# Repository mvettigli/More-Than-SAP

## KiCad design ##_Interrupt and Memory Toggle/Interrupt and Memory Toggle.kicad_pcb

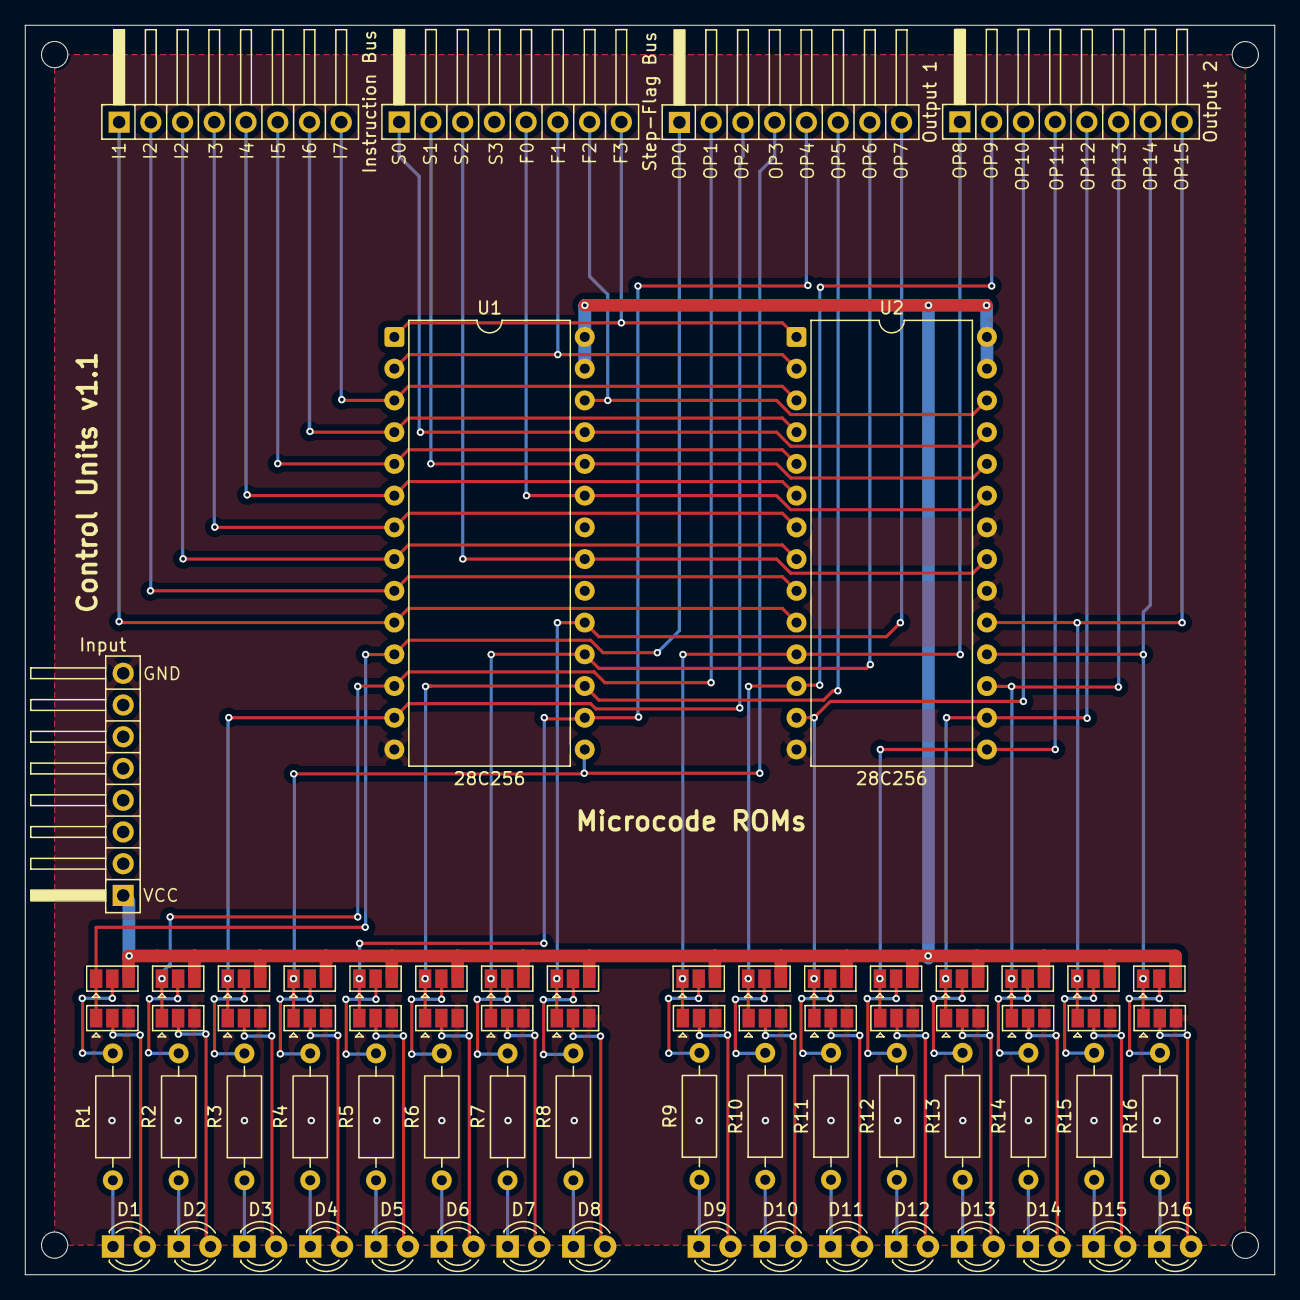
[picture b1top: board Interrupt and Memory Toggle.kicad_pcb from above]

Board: 2 copper layers, 100.0 x 100.0 mm, 71 parts (0 on the bottom side), 81 nets.

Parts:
D1, D2, D3, D4, D5, D6, D7, D8, D9, D10, D11, D12, D13, D14, D15, D16: YEL; LED_D3.0mm
J1: Input; PinHeader_1x08_P2.54mm_Horizontal
J2: Instruction Bus; PinHeader_1x08_P2.54mm_Horizontal
J3: Step-Flag Bus; PinHeader_1x08_P2.54mm_Horizontal
J4: Output 1; PinHeader_1x08_P2.54mm_Horizontal
J5: Output 2; PinHeader_1x08_P2.54mm_Horizontal
JP1, JP2, JP3, JP4, JP5, JP6, JP7, JP8, JP9, JP10, JP11, JP12, JP13, JP14, JP15, JP16, JP17, JP18, JP19, JP20, JP21, JP22, JP23, JP24, JP25, JP26, JP27, JP28, JP29, JP30, JP31, JP32: SolderJumper-3_P1.3mm_Open_Pad1.0x1.5mm
R1, R2, R3, R4, R5, R6, R7, R8, R9, R10, R11, R12, R13, R14, R15, R16: 220; R_Axial_DIN0207_L6.3mm_D2.5mm_P10.16mm_Horizontal
U1, U2: 28C256; DIP-28_W15.24mm

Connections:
/F0: J3.5, U1.23 (A11), U2.23 (A11)
/F1: J3.6, U1.2 (A12), U2.2 (A12)
/F2: J3.7, U1.26 (A13), U2.26 (A13)
/F3: J3.8, U1.1 (A14), U2.1 (A14)
/GND: J1.8, JP1.3 (B), JP3.3 (B), JP5.3 (B), JP7.3 (B), JP9.3 (B), JP11.3 (B), JP13.3 (B), JP15.3 (B), JP17.3 (B), JP19.3 (B), JP21.3 (B), JP23.3 (B), JP25.3 (B), JP27.3 (B), JP29.3 (B), JP31.3 (B), U1.14 (GND), U1.20 (~CS), U1.22 (~OE), U2.14 (GND), U2.20 (~CS), U2.22 (~OE)
/I0: J2.1, U1.10 (A0), U2.10 (A0)
/I1: J2.2, U1.9 (A1), U2.9 (A1)
/I2: J2.3, U1.8 (A2), U2.8 (A2)
/I3: J2.4, U1.7 (A3), U2.7 (A3)
/I4: J2.5, U1.6 (A4), U2.6 (A4)
/I5: J2.6, U1.5 (A5), U2.5 (A5)
/I6: J2.7, U1.4 (A6), U2.4 (A6)
/I7: J2.8, U1.3 (A7), U2.3 (A7)
/OP0: J4.1, JP1.1 (A), JP2.1 (A), U1.11 (D0)
/OP1: J4.2, JP3.1 (A), JP4.1 (A), U1.12 (D1)
/OP2: J4.3, JP5.1 (A), JP6.1 (A), U1.13 (D2)
/OP3: J4.4, JP7.1 (A), JP8.1 (A), U1.15 (D3)
/OP4: J4.5, JP9.1 (A), JP10.1 (A), U1.16 (D4)
/OP5: J4.6, JP11.1 (A), JP12.1 (A), U1.17 (D5)
/OP6: J4.7, JP13.1 (A), JP14.1 (A), U1.18 (D6)
/OP7: J4.8, JP15.1 (A), JP16.1 (A), U1.19 (D7)
/OP8: J5.1, JP17.1 (A), JP18.1 (A), U2.11 (D0)
/OP9: J5.2, JP19.1 (A), JP20.1 (A), U2.12 (D1)
/OP10: J5.3, JP21.1 (A), JP22.1 (A), U2.13 (D2)
/OP11: J5.4, JP23.1 (A), JP24.1 (A), U2.15 (D3)
/OP12: J5.5, JP25.1 (A), JP26.1 (A), U2.16 (D4)
/OP13: J5.6, JP27.1 (A), JP28.1 (A), U2.17 (D5)
/OP14: J5.7, JP31.1 (A), JP32.1 (A), U2.18 (D6)
/OP15: J5.8, JP29.1 (A), JP30.1 (A), U2.19 (D7)
/S0: J3.1, U1.25 (A8), U2.25 (A8)
/S1: J3.2, U1.24 (A9), U2.24 (A9)
/S2: J3.3, U1.21 (A10), U2.21 (A10)
/VCC: J1.1, JP2.3 (B), JP4.3 (B), JP6.3 (B), JP8.3 (B), JP10.3 (B), JP12.3 (B), JP14.3 (B), JP16.3 (B), JP18.3 (B), JP20.3 (B), JP22.3 (B), JP24.3 (B), JP26.3 (B), JP28.3 (B), JP30.3 (B), JP32.3 (B), U1.27 (~WE), U1.28 (VCC), U2.27 (~WE), U2.28 (VCC)
unnamed: D1.2 (A), JP1.2 (C)
unnamed: D1.1 (K), R1.1
unnamed: D2.2 (A), JP3.2 (C)
unnamed: D2.1 (K), R2.1
unnamed: D3.2 (A), JP5.2 (C)
unnamed: D3.1 (K), R3.1
unnamed: D4.2 (A), JP7.2 (C)
unnamed: D4.1 (K), R4.1
unnamed: D5.2 (A), JP9.2 (C)
unnamed: D5.1 (K), R5.1
unnamed: D6.2 (A), JP11.2 (C)
unnamed: D6.1 (K), R6.1
unnamed: D7.2 (A), JP13.2 (C)
unnamed: D7.1 (K), R7.1
unnamed: D8.2 (A), JP15.2 (C)
unnamed: D8.1 (K), R8.1
unnamed: D9.2 (A), JP17.2 (C)
unnamed: D9.1 (K), R9.1
unnamed: D10.2 (A), JP19.2 (C)
unnamed: D10.1 (K), R10.1
unnamed: D11.2 (A), JP21.2 (C)
unnamed: D11.1 (K), R11.1
unnamed: D12.2 (A), JP23.2 (C)
unnamed: D12.1 (K), R12.1
unnamed: D13.2 (A), JP25.2 (C)
unnamed: D13.1 (K), R13.1
unnamed: D14.2 (A), JP27.2 (C)
unnamed: D14.1 (K), R14.1
unnamed: D15.2 (A), JP29.2 (C)
unnamed: D15.1 (K), R15.1
unnamed: D16.2 (A), JP31.2 (C)
unnamed: D16.1 (K), R16.1
unnamed: JP2.2 (C), R1.2
unnamed: JP4.2 (C), R2.2
unnamed: JP6.2 (C), R3.2
unnamed: JP8.2 (C), R4.2
unnamed: JP10.2 (C), R5.2
unnamed: JP12.2 (C), R6.2
unnamed: JP14.2 (C), R7.2
unnamed: JP16.2 (C), R8.2
unnamed: JP18.2 (C), R9.2
unnamed: JP20.2 (C), R10.2
unnamed: JP22.2 (C), R11.2
unnamed: JP24.2 (C), R12.2
unnamed: JP26.2 (C), R13.2
unnamed: JP28.2 (C), R14.2
unnamed: JP30.2 (C), R15.2
unnamed: JP32.2 (C), R16.2

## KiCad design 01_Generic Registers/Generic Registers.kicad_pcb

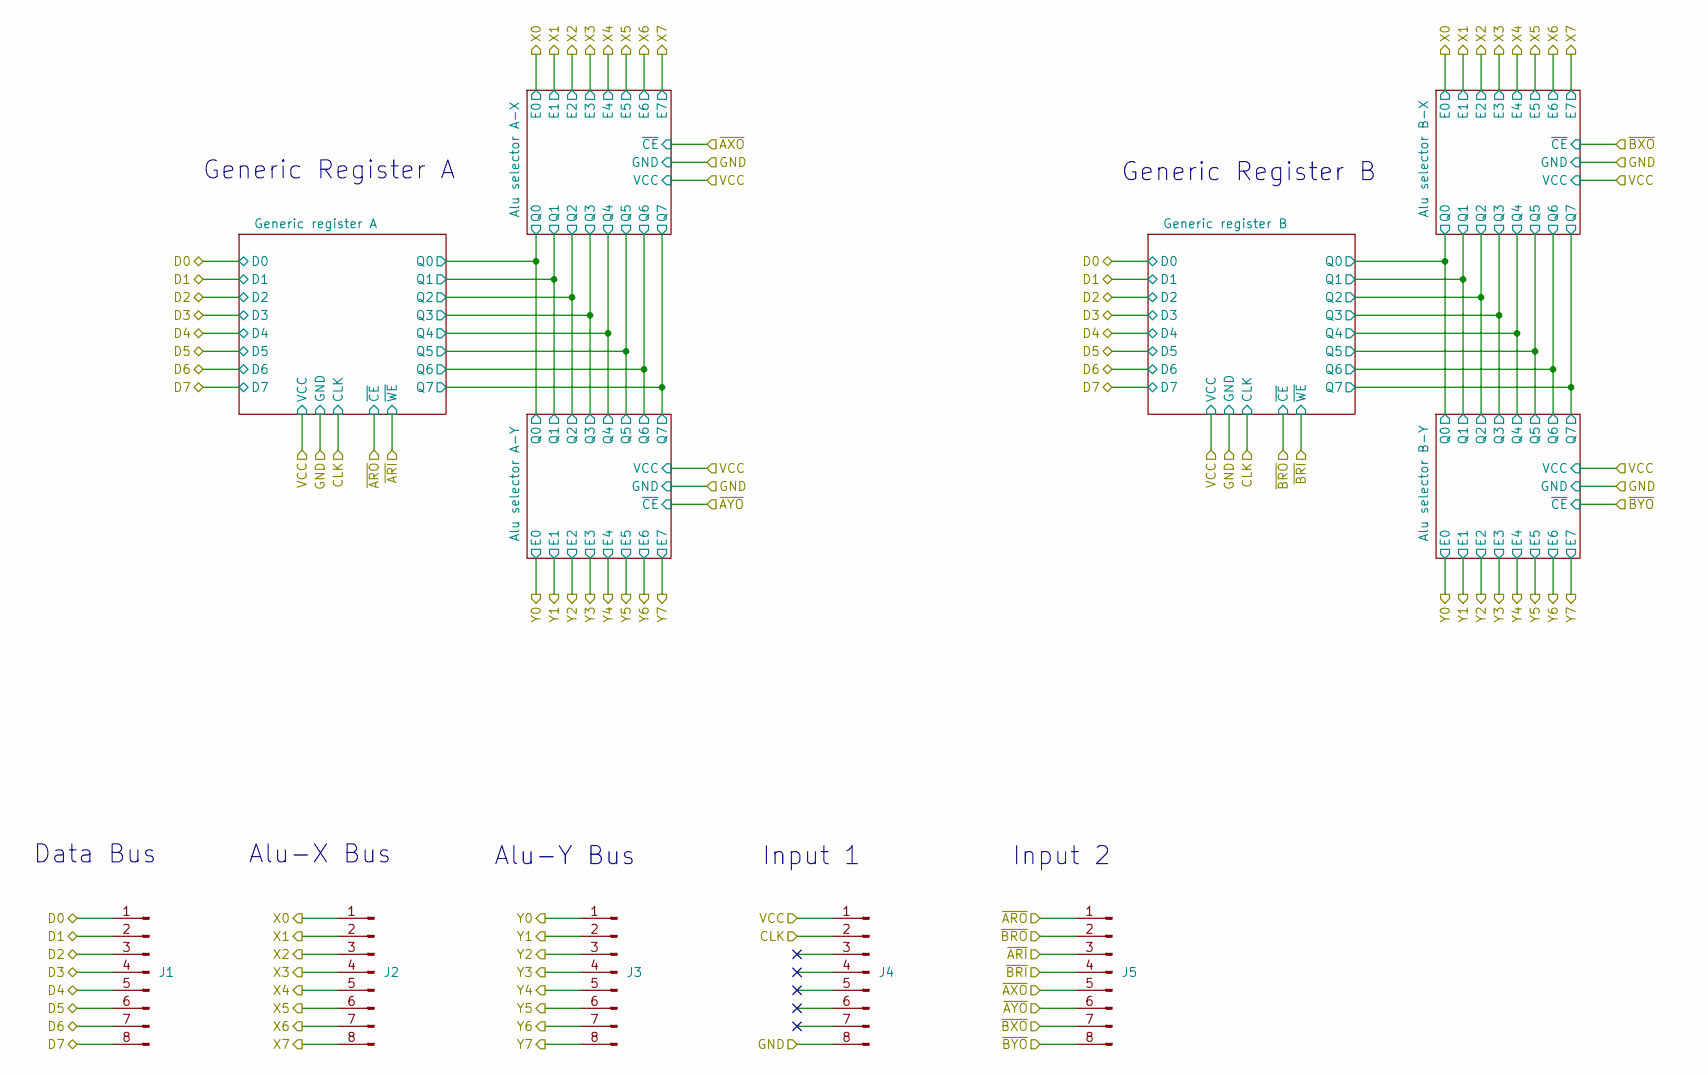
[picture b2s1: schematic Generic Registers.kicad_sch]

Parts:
J1: Data Bus; PinHeader_1x08_P2.54mm_Horizontal
J2: Alu-X Bus; PinHeader_1x08_P2.54mm_Horizontal
J3: Alu-Y Bus; PinHeader_1x08_P2.54mm_Horizontal
J4: Input 1; PinHeader_1x08_P2.54mm_Horizontal
J5: Input 2; PinHeader_1x08_P2.54mm_Horizontal

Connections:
/CLK: J4.2; also elsewhere on the board
/D0: J1.1; also elsewhere on the board
/D1: J1.2; also elsewhere on the board
/D2: J1.3; also elsewhere on the board
/D3: J1.4; also elsewhere on the board
/D4: J1.5; also elsewhere on the board
/D5: J1.6; also elsewhere on the board
/D6: J1.7; also elsewhere on the board
/D7: J1.8; also elsewhere on the board
/GND: J4.8; also elsewhere on the board
/VCC: J4.1; also elsewhere on the board
/X0: J2.1; also elsewhere on the board
/X1: J2.2; also elsewhere on the board
/X2: J2.3; also elsewhere on the board
/X3: J2.4; also elsewhere on the board
/X4: J2.5; also elsewhere on the board
/X5: J2.6; also elsewhere on the board
/X6: J2.7; also elsewhere on the board
/X7: J2.8; also elsewhere on the board
/Y0: J3.1; also elsewhere on the board
/Y1: J3.2; also elsewhere on the board
/Y2: J3.3; also elsewhere on the board
/Y3: J3.4; also elsewhere on the board
/Y4: J3.5; also elsewhere on the board
/Y5: J3.6; also elsewhere on the board
/Y6: J3.7; also elsewhere on the board
/Y7: J3.8; also elsewhere on the board
/~ARI: J5.3; also elsewhere on the board
/~ARO: J5.1; also elsewhere on the board
/~AXO: J5.5; also elsewhere on the board
/~AYO: J5.6; also elsewhere on the board
/~BRI: J5.4; also elsewhere on the board
/~BRO: J5.2; also elsewhere on the board
/~BXO: J5.7; also elsewhere on the board
/~BYO: J5.8; also elsewhere on the board

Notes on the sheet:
Generic Register A
Input 2
Alu-X Bus
Alu-Y Bus
Input 1
Data Bus
Generic Register B

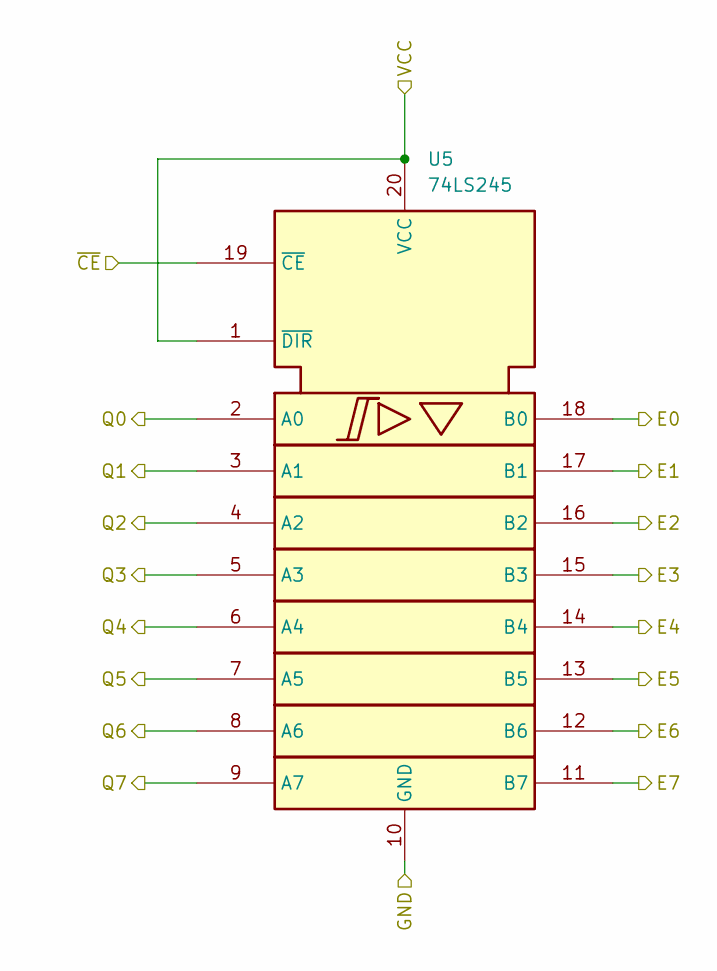
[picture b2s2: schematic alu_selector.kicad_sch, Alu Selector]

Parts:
U5: 74LS245; DIP-20_W7.62mm

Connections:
/Alu selector A-X/Q0: U5.2 (A0); also elsewhere on the board
/Alu selector A-X/Q1: U5.3 (A1); also elsewhere on the board
/Alu selector A-X/Q2: U5.4 (A2); also elsewhere on the board
/Alu selector A-X/Q3: U5.5 (A3); also elsewhere on the board
/Alu selector A-X/Q4: U5.6 (A4); also elsewhere on the board
/Alu selector A-X/Q5: U5.7 (A5); also elsewhere on the board
/Alu selector A-X/Q6: U5.8 (A6); also elsewhere on the board
/Alu selector A-X/Q7: U5.9 (A7); also elsewhere on the board
/GND: U5.10 (GND); also elsewhere on the board
/VCC: U5.1 (~DIR), U5.20 (VCC); also elsewhere on the board
/X0: U5.18 (B0); also elsewhere on the board
/X1: U5.17 (B1); also elsewhere on the board
/X2: U5.16 (B2); also elsewhere on the board
/X3: U5.15 (B3); also elsewhere on the board
/X4: U5.14 (B4); also elsewhere on the board
/X5: U5.13 (B5); also elsewhere on the board
/X6: U5.12 (B6); also elsewhere on the board
/X7: U5.11 (B7); also elsewhere on the board
/~AXO: U5.19 (~CE); also elsewhere on the board

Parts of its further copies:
U6, U7, U8: 74LS245; DIP-20_W7.62mm

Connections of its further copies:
/Alu selector A-X/Q0: U6.2 (A0); also elsewhere on the board
/Alu selector A-X/Q1: U6.3 (A1); also elsewhere on the board
/Alu selector A-X/Q2: U6.4 (A2); also elsewhere on the board
/Alu selector A-X/Q3: U6.5 (A3); also elsewhere on the board
/Alu selector A-X/Q4: U6.6 (A4); also elsewhere on the board
/Alu selector A-X/Q5: U6.7 (A5); also elsewhere on the board
/Alu selector A-X/Q6: U6.8 (A6); also elsewhere on the board
/Alu selector A-X/Q7: U6.9 (A7); also elsewhere on the board
/Alu selector B-X/Q0: U7.2 (A0), U8.2 (A0); also elsewhere on the board
/Alu selector B-X/Q1: U7.3 (A1), U8.3 (A1); also elsewhere on the board
/Alu selector B-X/Q2: U7.4 (A2), U8.4 (A2); also elsewhere on the board
/Alu selector B-X/Q3: U7.5 (A3), U8.5 (A3); also elsewhere on the board
/Alu selector B-X/Q4: U7.6 (A4), U8.6 (A4); also elsewhere on the board
/Alu selector B-X/Q5: U7.7 (A5), U8.7 (A5); also elsewhere on the board
/Alu selector B-X/Q6: U7.8 (A6), U8.8 (A6); also elsewhere on the board
/Alu selector B-X/Q7: U7.9 (A7), U8.9 (A7); also elsewhere on the board
/GND: U6.10 (GND), U7.10 (GND), U8.10 (GND); also elsewhere on the board
/VCC: U6.1 (~DIR), U6.20 (VCC), U7.1 (~DIR), U7.20 (VCC), U8.1 (~DIR), U8.20 (VCC); also elsewhere on the board
/X0: U7.18 (B0); also elsewhere on the board
/X1: U7.17 (B1); also elsewhere on the board
/X2: U7.16 (B2); also elsewhere on the board
/X3: U7.15 (B3); also elsewhere on the board
/X4: U7.14 (B4); also elsewhere on the board
/X5: U7.13 (B5); also elsewhere on the board
/X6: U7.12 (B6); also elsewhere on the board
/X7: U7.11 (B7); also elsewhere on the board
/Y0: U6.18 (B0), U8.18 (B0); also elsewhere on the board
/Y1: U6.17 (B1), U8.17 (B1); also elsewhere on the board
/Y2: U6.16 (B2), U8.16 (B2); also elsewhere on the board
/Y3: U6.15 (B3), U8.15 (B3); also elsewhere on the board
/Y4: U6.14 (B4), U8.14 (B4); also elsewhere on the board
/Y5: U6.13 (B5), U8.13 (B5); also elsewhere on the board
/Y6: U6.12 (B6), U8.12 (B6); also elsewhere on the board
/Y7: U6.11 (B7), U8.11 (B7); also elsewhere on the board
/~AYO: U6.19 (~CE); also elsewhere on the board
/~BXO: U7.19 (~CE); also elsewhere on the board
/~BYO: U8.19 (~CE); also elsewhere on the board

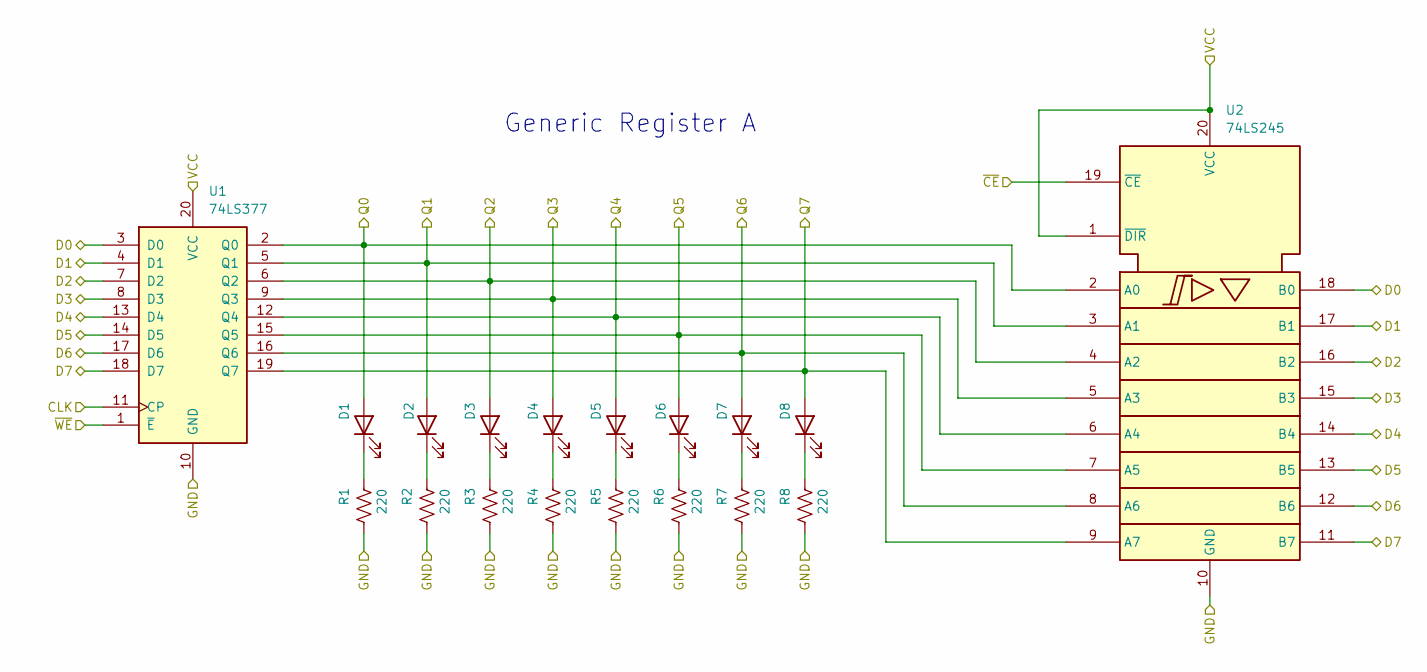
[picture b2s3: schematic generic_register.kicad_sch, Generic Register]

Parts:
D1, D2, D3, D4, D5, D6, D7, D8: RED; LED_D3.0mm
R1, R2, R3, R4, R5, R6, R7, R8: 220; R_Axial_DIN0207_L6.3mm_D2.5mm_P10.16mm_Horizontal
U1: 74LS377; DIP-20_W7.62mm
U2: 74LS245; DIP-20_W7.62mm

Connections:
/Alu selector A-X/Q0: D1.2 (A), U1.2 (Q0), U2.2 (A0); also elsewhere on the board
/Alu selector A-X/Q1: D2.2 (A), U1.5 (Q1), U2.3 (A1); also elsewhere on the board
/Alu selector A-X/Q2: D3.2 (A), U1.6 (Q2), U2.4 (A2); also elsewhere on the board
/Alu selector A-X/Q3: D4.2 (A), U1.9 (Q3), U2.5 (A3); also elsewhere on the board
/Alu selector A-X/Q4: D5.2 (A), U1.12 (Q4), U2.6 (A4); also elsewhere on the board
/Alu selector A-X/Q5: D6.2 (A), U1.15 (Q5), U2.7 (A5); also elsewhere on the board
/Alu selector A-X/Q6: D7.2 (A), U1.16 (Q6), U2.8 (A6); also elsewhere on the board
/Alu selector A-X/Q7: D8.2 (A), U1.19 (Q7), U2.9 (A7); also elsewhere on the board
/CLK: U1.11 (CP); also elsewhere on the board
/D0: U1.3 (D0), U2.18 (B0); also elsewhere on the board
/D1: U1.4 (D1), U2.17 (B1); also elsewhere on the board
/D2: U1.7 (D2), U2.16 (B2); also elsewhere on the board
/D3: U1.8 (D3), U2.15 (B3); also elsewhere on the board
/D4: U1.13 (D4), U2.14 (B4); also elsewhere on the board
/D5: U1.14 (D5), U2.13 (B5); also elsewhere on the board
/D6: U1.17 (D6), U2.12 (B6); also elsewhere on the board
/D7: U1.18 (D7), U2.11 (B7); also elsewhere on the board
/GND: R1.2, R2.2, R3.2, R4.2, R5.2, R6.2, R7.2, R8.2, U1.10 (GND), U2.10 (GND); also elsewhere on the board
/VCC: U1.20 (VCC), U2.1 (~DIR), U2.20 (VCC); also elsewhere on the board
/~ARI: U1.1 (~E); also elsewhere on the board
/~ARO: U2.19 (~CE); also elsewhere on the board
unnamed: D1.1 (K), R1.1
unnamed: D2.1 (K), R2.1
unnamed: D3.1 (K), R3.1
unnamed: D4.1 (K), R4.1
unnamed: D5.1 (K), R5.1
unnamed: D6.1 (K), R6.1
unnamed: D7.1 (K), R7.1
unnamed: D8.1 (K), R8.1

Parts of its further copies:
D9, D10, D11, D12, D13, D14, D15, D16: RED; LED_D3.0mm
R9, R10, R11, R12, R13, R14, R15, R16: 220; R_Axial_DIN0207_L6.3mm_D2.5mm_P10.16mm_Horizontal
U3: 74LS377; DIP-20_W7.62mm
U4: 74LS245; DIP-20_W7.62mm

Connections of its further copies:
/Alu selector B-X/Q0: D9.2 (A), U3.2 (Q0), U4.2 (A0); also elsewhere on the board
/Alu selector B-X/Q1: D10.2 (A), U3.5 (Q1), U4.3 (A1); also elsewhere on the board
/Alu selector B-X/Q2: D11.2 (A), U3.6 (Q2), U4.4 (A2); also elsewhere on the board
/Alu selector B-X/Q3: D12.2 (A), U3.9 (Q3), U4.5 (A3); also elsewhere on the board
/Alu selector B-X/Q4: D13.2 (A), U3.12 (Q4), U4.6 (A4); also elsewhere on the board
/Alu selector B-X/Q5: D14.2 (A), U3.15 (Q5), U4.7 (A5); also elsewhere on the board
/Alu selector B-X/Q6: D15.2 (A), U3.16 (Q6), U4.8 (A6); also elsewhere on the board
/Alu selector B-X/Q7: D16.2 (A), U3.19 (Q7), U4.9 (A7); also elsewhere on the board
/CLK: U3.11 (CP); also elsewhere on the board
/D0: U3.3 (D0), U4.18 (B0); also elsewhere on the board
/D1: U3.4 (D1), U4.17 (B1); also elsewhere on the board
/D2: U3.7 (D2), U4.16 (B2); also elsewhere on the board
/D3: U3.8 (D3), U4.15 (B3); also elsewhere on the board
/D4: U3.13 (D4), U4.14 (B4); also elsewhere on the board
/D5: U3.14 (D5), U4.13 (B5); also elsewhere on the board
/D6: U3.17 (D6), U4.12 (B6); also elsewhere on the board
/D7: U3.18 (D7), U4.11 (B7); also elsewhere on the board
/GND: R9.2, R10.2, R11.2, R12.2, R13.2, R14.2, R15.2, R16.2, U3.10 (GND), U4.10 (GND); also elsewhere on the board
/VCC: U3.20 (VCC), U4.1 (~DIR), U4.20 (VCC); also elsewhere on the board
/~BRI: U3.1 (~E); also elsewhere on the board
/~BRO: U4.19 (~CE); also elsewhere on the board
unnamed: D9.1 (K), R9.1
unnamed: D10.1 (K), R10.1
unnamed: D11.1 (K), R11.1
unnamed: D12.1 (K), R12.1
unnamed: D13.1 (K), R13.1
unnamed: D14.1 (K), R14.1
unnamed: D15.1 (K), R15.1
unnamed: D16.1 (K), R16.1

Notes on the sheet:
Generic Register A

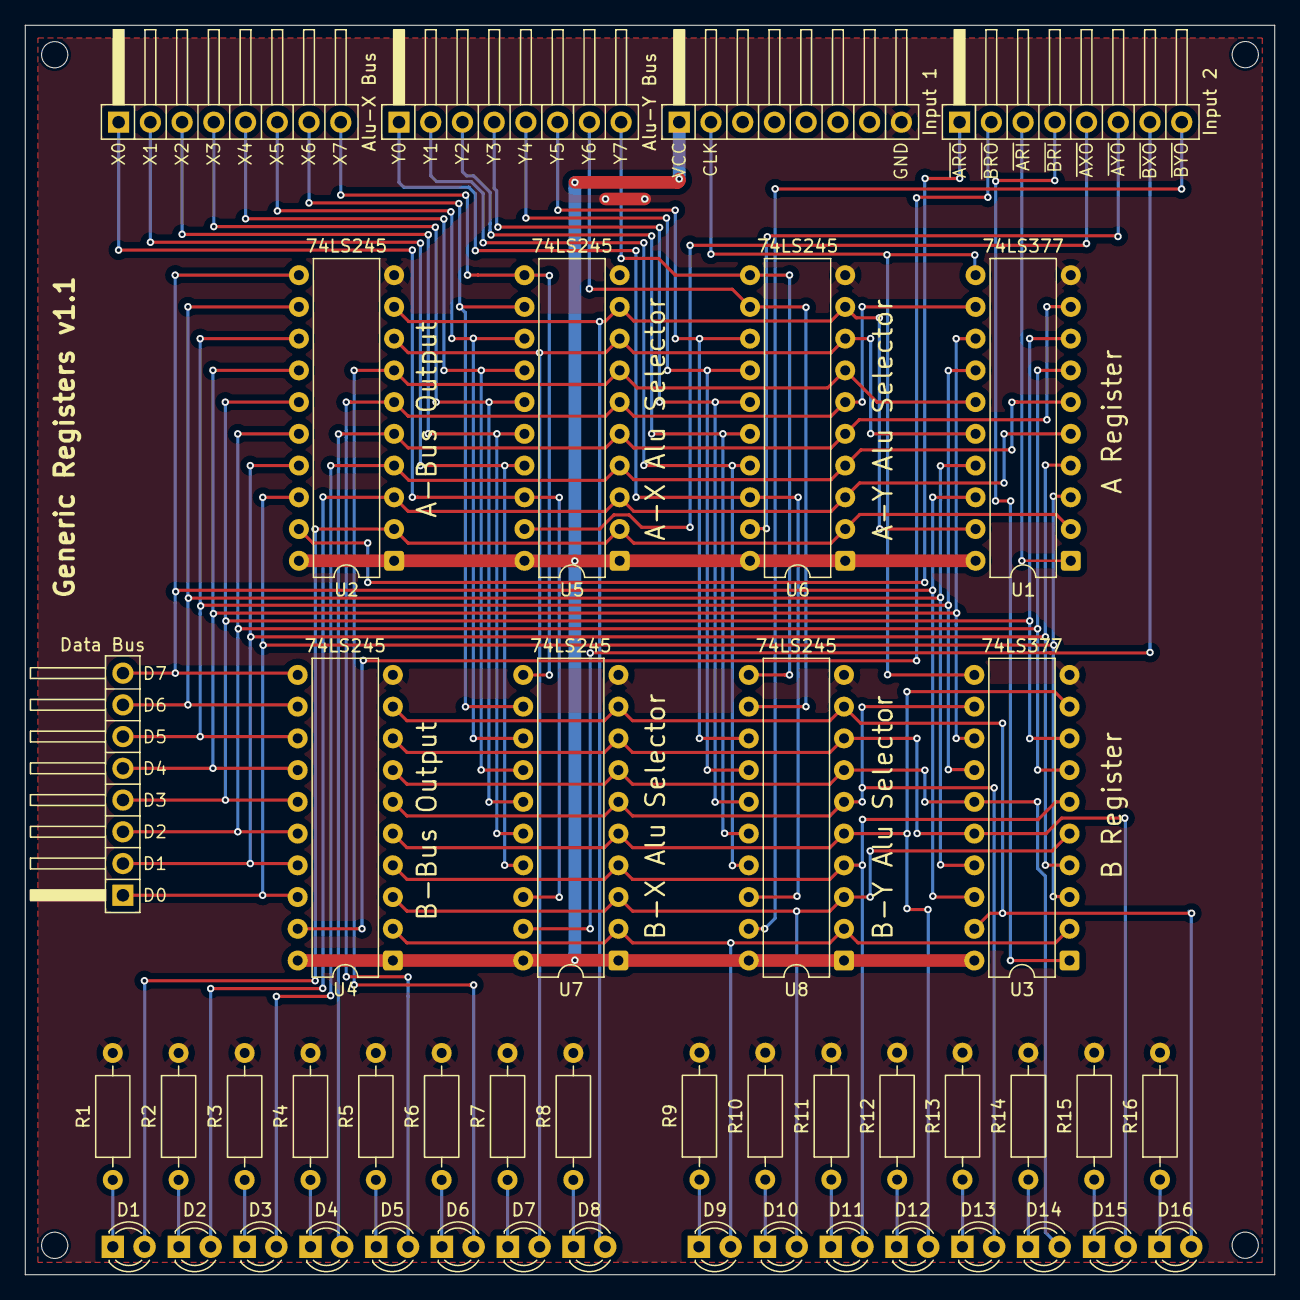
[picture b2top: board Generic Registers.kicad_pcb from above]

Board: 2 copper layers, 100.0 x 100.0 mm, 49 parts (0 on the bottom side), 67 nets.

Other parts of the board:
LU: MountingHole_2.1mm
LU#2, LU#3, LU#4: MountingHole_2.1mm

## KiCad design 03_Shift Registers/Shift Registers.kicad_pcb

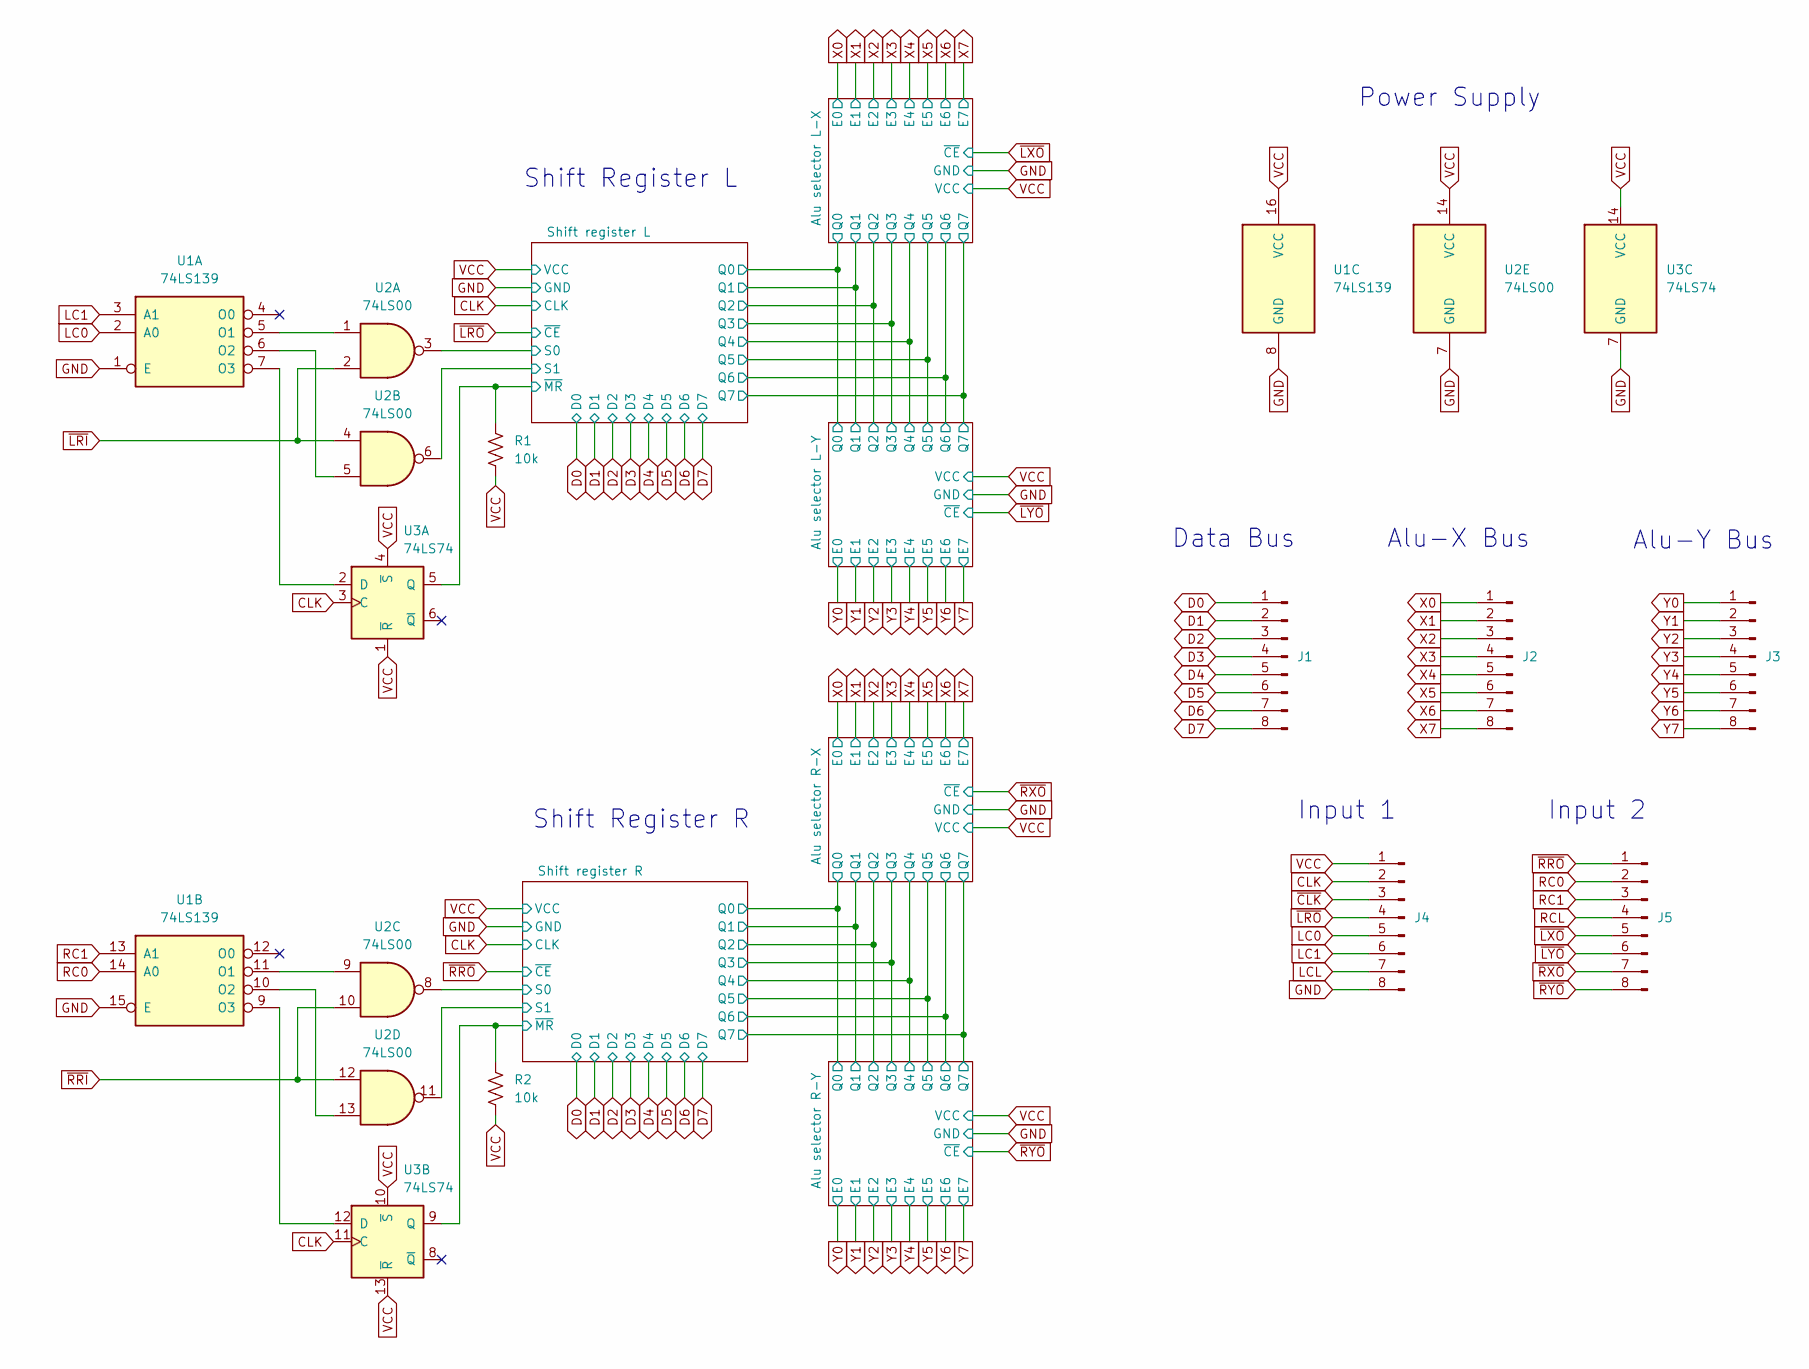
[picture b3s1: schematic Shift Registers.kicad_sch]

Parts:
J1: Data bus; PinHeader_1x08_P2.54mm_Horizontal
J2: Alu-X bus; PinHeader_1x08_P2.54mm_Horizontal
J3: Alu-Y bus; PinHeader_1x08_P2.54mm_Horizontal
J4: Input 1; PinHeader_1x08_P2.54mm_Horizontal
J5: Input 2; PinHeader_1x08_P2.54mm_Horizontal
R1, R2: 10k
U1: 74LS139; DIP-16_W7.62mm
U2: 74LS00; DIP-14_W7.62mm
U3: 74LS74

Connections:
/Shift register L/S0: U2.3; also elsewhere on the board
/Shift register L/S1: U2.6; also elsewhere on the board
/Shift register R/S0: U2.8; also elsewhere on the board
/Shift register R/S1: U2.11; also elsewhere on the board
CLK: J4.2, U3.3 (C), U3.11 (C); also elsewhere on the board
D0: J1.1; also elsewhere on the board
D1: J1.2; also elsewhere on the board
D2: J1.3; also elsewhere on the board
D3: J1.4; also elsewhere on the board
D4: J1.5; also elsewhere on the board
D5: J1.6; also elsewhere on the board
D6: J1.7; also elsewhere on the board
D7: J1.8; also elsewhere on the board
GND: J4.8, U1.1 (E), U1.8 (GND), U1.15 (E), U2.7 (GND), U3.7 (GND); also elsewhere on the board
LC0: J4.5, U1.2 (A0)
LC1: J4.6, U1.3 (A1)
LCL: J4.7
unnamed: R1.1, U3.5 (Q)
unnamed: R2.1, U3.9 (Q)
unnamed: U1.5 (O1), U2.1
unnamed: U1.6 (O2), U2.5
unnamed: U1.7 (O3), U3.2 (D)
unnamed: U1.11 (O1), U2.9
unnamed: U1.10 (O2), U2.13
unnamed: U1.9 (O3), U3.12 (D)
RC0: J5.2, U1.14 (A0)
RC1: J5.3, U1.13 (A1)
RCL: J5.4
VCC: J4.1, R1.2, R2.2, U1.16 (VCC), U2.14 (VCC), U3.1 (~R), U3.4 (~S), U3.10 (~S), U3.13 (~R), U3.14 (VCC); also elsewhere on the board
X0: J2.1; also elsewhere on the board
X1: J2.2; also elsewhere on the board
X2: J2.3; also elsewhere on the board
X3: J2.4; also elsewhere on the board
X4: J2.5; also elsewhere on the board
X5: J2.6; also elsewhere on the board
X6: J2.7; also elsewhere on the board
X7: J2.8; also elsewhere on the board
Y0: J3.1; also elsewhere on the board
Y1: J3.2; also elsewhere on the board
Y2: J3.3; also elsewhere on the board
Y3: J3.4; also elsewhere on the board
Y4: J3.5; also elsewhere on the board
Y5: J3.6; also elsewhere on the board
Y6: J3.7; also elsewhere on the board
Y7: J3.8; also elsewhere on the board
~CLK: J4.3
~LRI: U2.2, U2.4
~LRO: J4.4; also elsewhere on the board
~LXO: J5.5; also elsewhere on the board
~LYO: J5.6; also elsewhere on the board
~RRI: U2.10, U2.12
~RRO: J5.1; also elsewhere on the board
~RXO: J5.7; also elsewhere on the board
~RYO: J5.8; also elsewhere on the board

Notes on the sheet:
Power Supply
Input 1
Alu-X Bus
Input 2
Shift Register R
Alu-Y Bus
Data Bus
Shift Register L

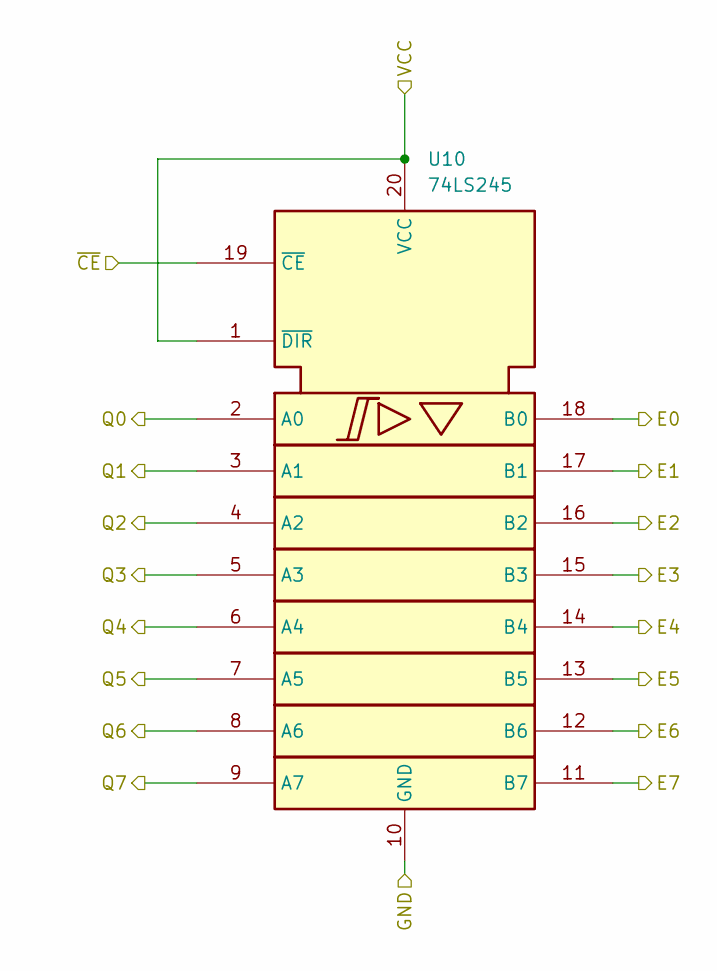
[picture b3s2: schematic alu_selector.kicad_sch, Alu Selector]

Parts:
U10: 74LS245; DIP-20_W7.62mm

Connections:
/Alu selector L-X/Q0: U10.2 (A0); also elsewhere on the board
/Alu selector L-X/Q1: U10.3 (A1); also elsewhere on the board
/Alu selector L-X/Q2: U10.4 (A2); also elsewhere on the board
/Alu selector L-X/Q3: U10.5 (A3); also elsewhere on the board
/Alu selector L-X/Q4: U10.6 (A4); also elsewhere on the board
/Alu selector L-X/Q5: U10.7 (A5); also elsewhere on the board
/Alu selector L-X/Q6: U10.8 (A6); also elsewhere on the board
/Alu selector L-X/Q7: U10.9 (A7); also elsewhere on the board
GND: U10.10 (GND); also elsewhere on the board
VCC: U10.1 (~DIR), U10.20 (VCC); also elsewhere on the board
X0: U10.18 (B0); also elsewhere on the board
X1: U10.17 (B1); also elsewhere on the board
X2: U10.16 (B2); also elsewhere on the board
X3: U10.15 (B3); also elsewhere on the board
X4: U10.14 (B4); also elsewhere on the board
X5: U10.13 (B5); also elsewhere on the board
X6: U10.12 (B6); also elsewhere on the board
X7: U10.11 (B7); also elsewhere on the board
~LXO: U10.19 (~CE); also elsewhere on the board

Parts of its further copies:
U11, U12, U13: 74LS245; DIP-20_W7.62mm

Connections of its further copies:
/Alu selector L-X/Q0: U11.2 (A0); also elsewhere on the board
/Alu selector L-X/Q1: U11.3 (A1); also elsewhere on the board
/Alu selector L-X/Q2: U11.4 (A2); also elsewhere on the board
/Alu selector L-X/Q3: U11.5 (A3); also elsewhere on the board
/Alu selector L-X/Q4: U11.6 (A4); also elsewhere on the board
/Alu selector L-X/Q5: U11.7 (A5); also elsewhere on the board
/Alu selector L-X/Q6: U11.8 (A6); also elsewhere on the board
/Alu selector L-X/Q7: U11.9 (A7); also elsewhere on the board
/Alu selector R-X/Q0: U12.2 (A0), U13.2 (A0); also elsewhere on the board
/Alu selector R-X/Q1: U12.3 (A1), U13.3 (A1); also elsewhere on the board
/Alu selector R-X/Q2: U12.4 (A2), U13.4 (A2); also elsewhere on the board
/Alu selector R-X/Q3: U12.5 (A3), U13.5 (A3); also elsewhere on the board
/Alu selector R-X/Q4: U12.6 (A4), U13.6 (A4); also elsewhere on the board
/Alu selector R-X/Q5: U12.7 (A5), U13.7 (A5); also elsewhere on the board
/Alu selector R-X/Q6: U12.8 (A6), U13.8 (A6); also elsewhere on the board
/Alu selector R-X/Q7: U12.9 (A7), U13.9 (A7); also elsewhere on the board
GND: U11.10 (GND), U12.10 (GND), U13.10 (GND); also elsewhere on the board
VCC: U11.1 (~DIR), U11.20 (VCC), U12.1 (~DIR), U12.20 (VCC), U13.1 (~DIR), U13.20 (VCC); also elsewhere on the board
X0: U12.18 (B0); also elsewhere on the board
X1: U12.17 (B1); also elsewhere on the board
X2: U12.16 (B2); also elsewhere on the board
X3: U12.15 (B3); also elsewhere on the board
X4: U12.14 (B4); also elsewhere on the board
X5: U12.13 (B5); also elsewhere on the board
X6: U12.12 (B6); also elsewhere on the board
X7: U12.11 (B7); also elsewhere on the board
Y0: U11.18 (B0), U13.18 (B0); also elsewhere on the board
Y1: U11.17 (B1), U13.17 (B1); also elsewhere on the board
Y2: U11.16 (B2), U13.16 (B2); also elsewhere on the board
Y3: U11.15 (B3), U13.15 (B3); also elsewhere on the board
Y4: U11.14 (B4), U13.14 (B4); also elsewhere on the board
Y5: U11.13 (B5), U13.13 (B5); also elsewhere on the board
Y6: U11.12 (B6), U13.12 (B6); also elsewhere on the board
Y7: U11.11 (B7), U13.11 (B7); also elsewhere on the board
~LYO: U11.19 (~CE); also elsewhere on the board
~RXO: U12.19 (~CE); also elsewhere on the board
~RYO: U13.19 (~CE); also elsewhere on the board
